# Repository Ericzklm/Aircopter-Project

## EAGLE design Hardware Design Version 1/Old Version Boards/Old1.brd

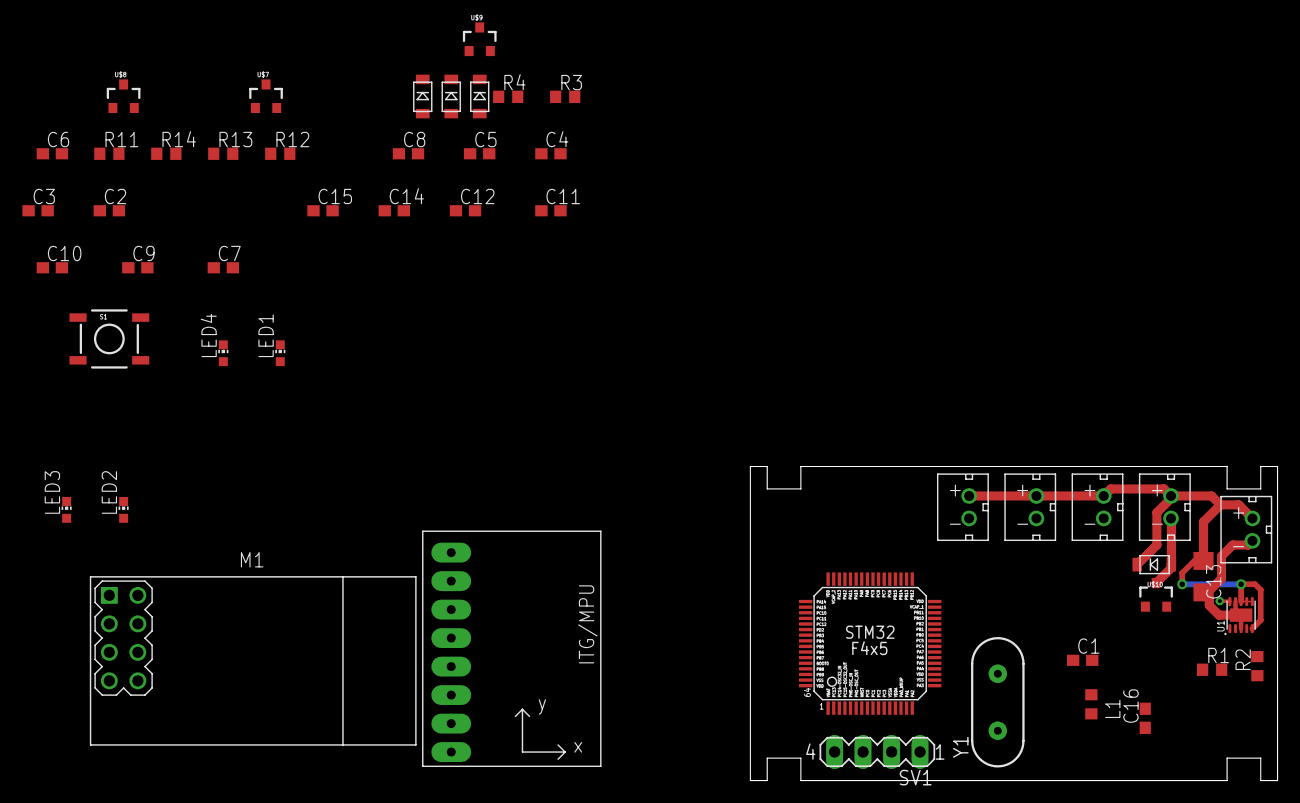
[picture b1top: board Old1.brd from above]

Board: 2 copper layers, 47.0 x 28.0 mm, 49 parts (0 on the bottom side), 37 nets.

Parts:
C1, C7, C9, C10, C11, C12: 100nF; C0603
C2, C8: 10uF; C0603
C3: 22uF; C0603
C4, C5: 16pF; C0603
C6: 1uF; C0603
C13: 100uF; C1206
C14, C15: 2.2uF; C0603
C16: 4.7uF; C0603
L1: 2.2uH; L0603
LED1, LED4: Blue; CHIP-LED0603
LED2, LED3: Green; CHIP-LED0603
M1: WIRELESS-NRF24L01
R1: 487k; R0603
R2: 86.6k; R0603
R3, R4: 10k; R0603
R11, R12, R13, R14: 1k; R0603
S1: SWITCH-MOMENTARY-2SMD; TACTILE-SWITCH-SMD
SV1: MA04-1
U1: RT6150AGQW; SON50P250X250X80-11N
U2: GY-521MPU6050; GY-521
U$1: STM32F405/415_LQFP64
U$2, U$3, U$4, U$5, U$6: JST_CONNECTOR_FEMALE
U$7, U$8, U$9, U$10: N-CHANNEL-MOSFET-IRLML6244TRPBF; SOT23-3
U$11, U$12, U$13, U$14: DB2W40300L; MINI2-F3-B
Y1: 12MHz; HC49US

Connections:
3.7V: C2.2, C13.1, R3.2, U1.5, U1.6, U1.7, U1.8, U$2.+, U$3.+, U$4.+, U$5.+, U$6.+, U$11.NEG, U$12.NEG, U$13.NEG, U$14.NEG
ANALOG: R3.1, R4.2, U$1.PA1, U$1.PB1
CE: M1.3, U$1.PA7
CSN: M1.4, U$1.PA6
FB: R1.2, R2.1, U1.10
GND: C1.1, C2.1, C3.2, C4.2, C5.2, C6.1, C7.1, C8.1, C9.1, C10.1, C11.1, C12.1, C13.2, C14.2, C15.1, C16.1, LED1.C, LED2.C, LED3.C, LED4.C, M1.1, R2.2, R4.1, S1.1, SV1.4, U1.3, U1.9, U1.11, U2.GND, U$1.BOOT0, U$1.VSSA, U$1.VSS_0, U$1.VSS_1, U$2.-, U$7.2, U$8.2, U$9.2, U$10.2
LED_MISO: R14.1, U$1.PC9
LED_PWR: R11.1, U$1.PC6
LED_RST: R12.1, U$1.PC7
LED_SWDIO: R13.1, U$1.PC8
MISO: M1.7, U$1.PC11
MOSI: M1.6, U$1.PC12
unnamed: L1.2, U1.4
unnamed: L1.1, U1.2
unnamed: U$3.-, U$9.3, U$11.POS
unnamed: U$5.-, U$8.3, U$12.POS
unnamed: U$4.-, U$7.3, U$13.POS
unnamed: U$6.-, U$10.3, U$14.POS
unnamed: LED1.A, R11.2
unnamed: LED4.A, R12.2
unnamed: LED2.A, R13.2
unnamed: LED3.A, R14.2
unnamed: C15.2, U$1.VCAP_1
unnamed: C14.1, U$1.VCAP_2
OSC_IN: C5.1, U$1.PH0, Y1.2
OSC_OUT: C4.1, U$1.PH1, Y1.1
RESET: C6.2, S1.3, SV1.3, U$1.NRST
SCK: M1.5, U$1.PC10
SCL: U2.SCL, U$1.PB10
SDA: U2.SDA, U$1.PB11
SWCLK: SV1.1, U$1.PA14
SWDIO: SV1.2, U$1.PA13
TIM1: U$1.PA8, U$10.1
TIM2: U$1.PA9, U$8.1
TIM3: U$1.PA10, U$7.1
TIM4: U$1.PA11, U$9.1
VOUT: C1.2, C3.1, C7.2, C8.2, C9.2, C10.2, C11.2, C12.2, C16.2, M1.2, R1.1, U1.1, U2.VCC, U$1.VDDA, U$1.VDD_0, U$1.VDD_1, U$1.VDD_2, U$1.VDD_3
